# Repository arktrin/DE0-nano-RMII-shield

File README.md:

# DE0-nano_RMII
DE0-nano RMII shield

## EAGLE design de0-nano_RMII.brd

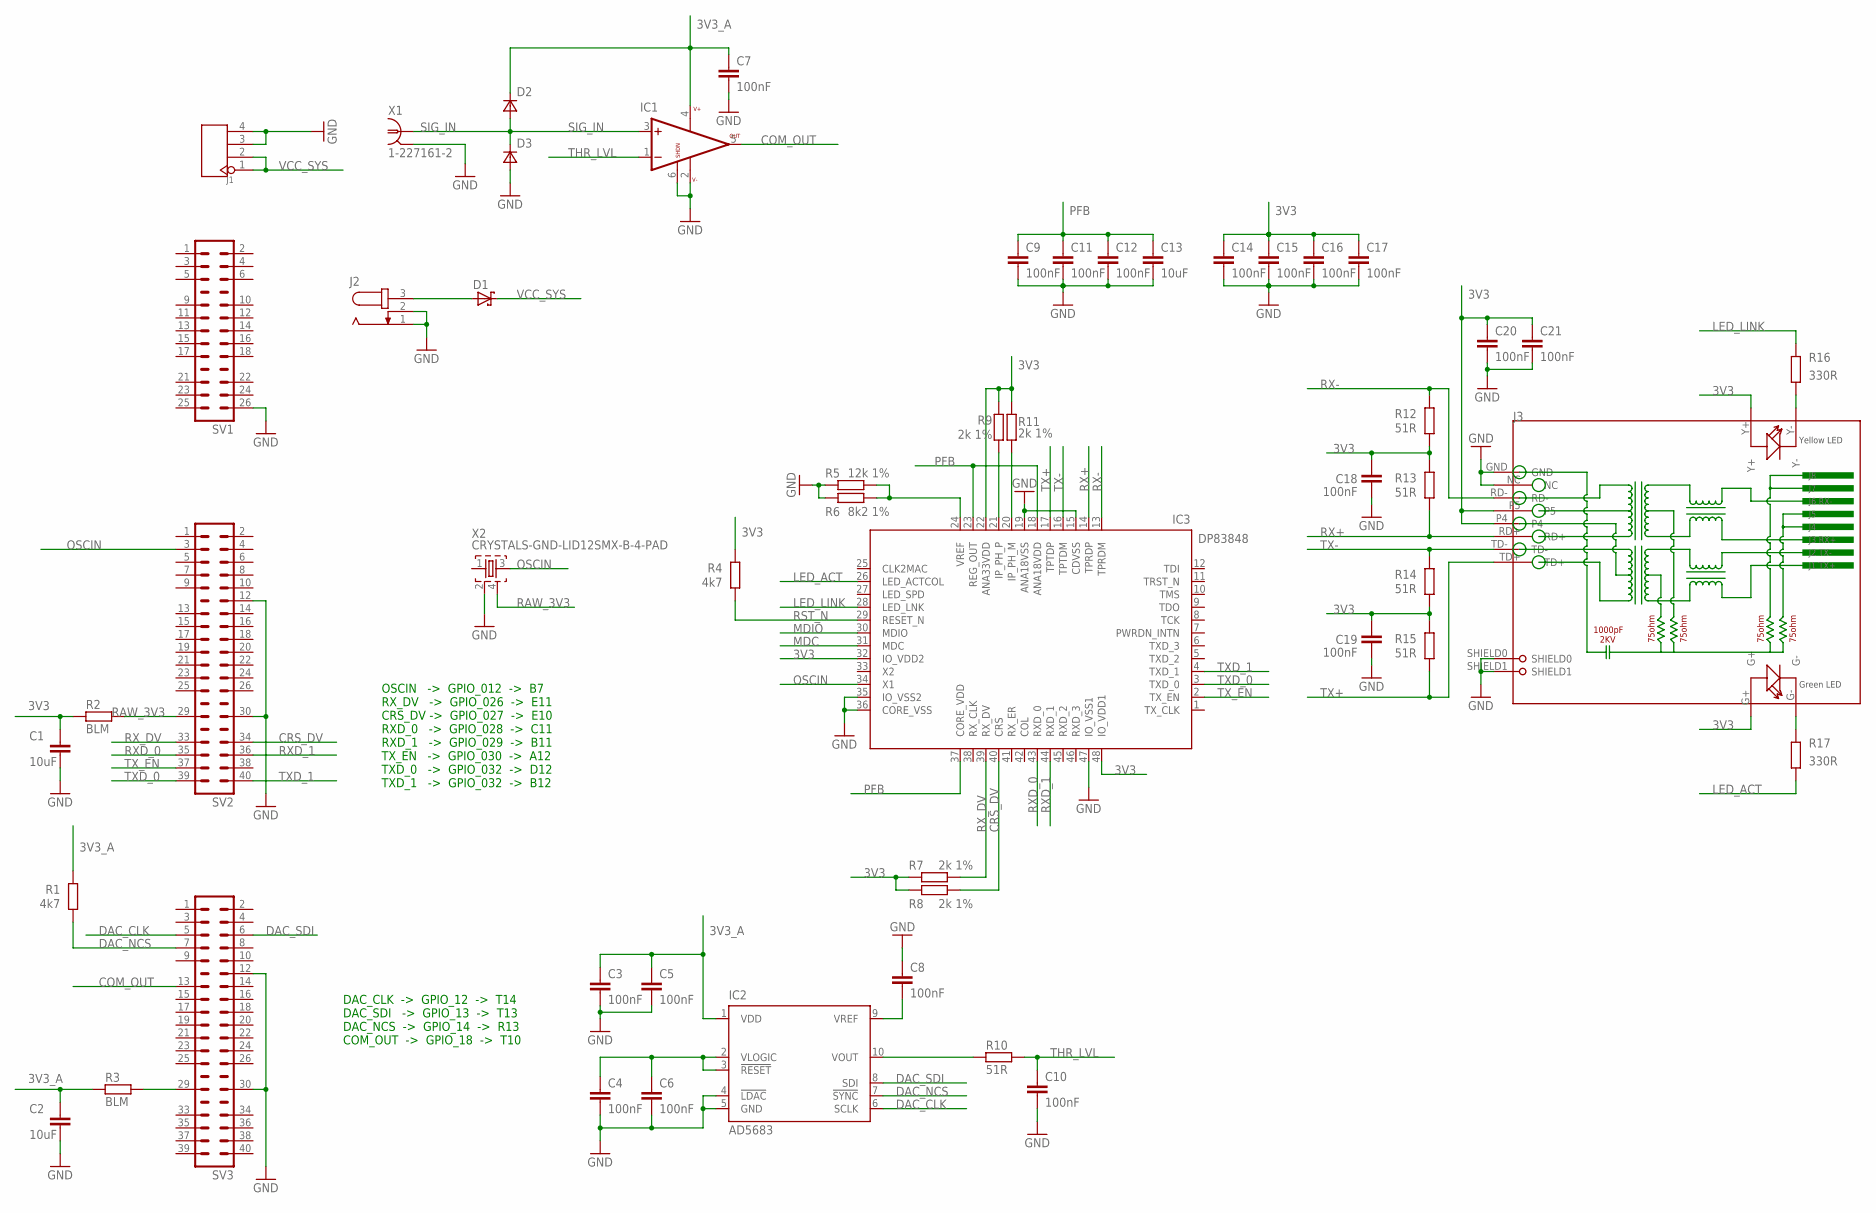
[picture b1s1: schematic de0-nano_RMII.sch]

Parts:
C1, C2, C13: 10uF; C0805
C3, C4, C5, C6, C7, C8, C9, C10, C11, C12, C14, C15, C16, C17, C18, C19, C20, C21: 100nF; C0603
D1: SCHOTTKY-DIODESMC; SMC
D2, D3: DSOD323; SOD323
IC1: LT1719; TSOT23-6
IC2: AD5683; SO10
IC3: DP83848; LQFP48
J1: HEADER-4P-60/35MIL; 4P-65/35MIL
J2: JACK-PLUG1; SPC4078
J3: RJ45-HR911105A-HR911105A; RJ45
R1, R4: 4k7; R0603
R2, R3: BLM; R0603
R5: 12k 1%; R0603
R6: 8k2 1%; R0603
R7, R8, R9, R11: 2k 1%; R0603
R10, R12, R13, R14, R15: 51R; R0603
R16, R17: 330R; R0603
SV1: MA13-2_ALT
SV2, SV3: MA20-2_ALT
X1: 1-227161-2; AMP_227161
X2: CRYSTALS-GND-LID12SMX-B-4-PAD; 7.5X5-4-PAD

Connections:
3V3: C1.1, C14.1, C15.1, C16.1, C17.1, C18.1, C19.1, C20.1, C21.1, IC3.22 (ANA33VDD), IC3.32 (IO_VDD2), IC3.48 (IO_VDD1), J3.G+, J3.P4, J3.P5, J3.Y+, R2.1, R4.1, R7.2, R8.2, R9.2, R11.2, R12.2, R13.1, R14.2, R15.1
3V3_A: C2.1, C3.1, C5.1, C7.1, D2.1 (C), IC1.4 (V+), IC2.1 (VDD), R1.1, R3.1
COM_OUT: IC1.5 (OUT), SV3.13
CRS_DV: IC3.40 (CRS), R8.1, SV2.34
DAC_CLK: IC2.6 (SCLK), SV3.5
DAC_NCS: IC2.7 (!SYNC), R1.2, SV3.7
DAC_SDI: IC2.8 (SDI), SV3.6
GND: C1.2, C2.2, C3.2, C4.2, C5.2, C6.2, C7.2, C8.2, C9.2, C10.2, C11.2, C12.2, C13.2, C14.2, C15.2, C16.2, C17.2, C18.2, C19.2, C20.2, C21.2, D3.2 (A), IC1.2 (V-), IC1.6 (SHDN), IC2.4 (!LDAC), IC2.5 (GND), IC3.15 (CDVSS), IC3.19 (ANA18VSS), IC3.35 (IO_VSS2), IC3.36 (CORE_VSS), IC3.47 (IO_VSS1), J1.3, J1.4, J2.1, J2.2, J3.GND, J3.NC, J3.SHIELD0, J3.SHIELD1, R5.2, R6.2, SV1.26, SV2.12, SV2.30, SV3.12, SV3.30, X1.2, X2.2
LED_ACT: IC3.26 (LED_ACTCOL), R17.1
LED_LINK: IC3.28 (LED_LNK), R16.2
MDC: IC3.31 (MDC)
MDIO: IC3.30 (MDIO)
unnamed: R3.2, SV3.29
unnamed: IC3.21 (IP_PH_P), R9.1
unnamed: J3.Y-, R16.1
unnamed: IC3.20 (IP_PH_M), R11.1
unnamed: J3.G-, R17.2
unnamed: IC2.10 (VOUT), R10.1
unnamed: IC3.24 (VREF), R5.1, R6.1
unnamed: C8.1, IC2.9 (VREF)
OSCIN: IC3.34 (X1), SV2.3, X2.3
PFB: C9.1, C11.1, C12.1, C13.1, IC3.18 (ANA18VDD), IC3.23 (REG_OUT), IC3.37 (CORE_VDD)
RAW_3V3: R2.2, SV2.29, X2.4
RST_N: IC3.29 (RESET_N), R4.2
RX+: IC3.14 (TPRDP), J3.RD+, R13.2
RX-: IC3.13 (TPRDM), J3.RD-, R12.1
RXD_0: IC3.43 (RXD_0), SV2.35
RXD_1: IC3.44 (RXD_1), SV2.36
RX_DV: IC3.39 (RX_DV), R7.1, SV2.33
SIG_IN: D2.2 (A), D3.1 (C), IC1.3 (+IN), X1.1
THR_LVL: C10.1, IC1.1 (-IN), R10.2
TX+: IC3.17 (TPTDP), J3.TD+, R15.2
TX-: IC3.16 (TPTDM), J3.TD-, R14.1
TXD_0: IC3.3 (TXD_0), SV2.39
TXD_1: IC3.4 (TXD_1), SV2.40
TX_EN: IC3.2 (TX_EN), SV2.37
VCC_SYS: D1.C, J1.1, J1.2
VLOGIC: C4.1, C6.1, IC2.2 (VLOGIC), IC2.3 (!RESET)
V_RAW: D1.A, J2.3

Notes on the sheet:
OSCIN -> GPIO_012 -> B7 RX_DV -> GPIO_026 -> E11 CRS_DV -> GPIO_027 -> E10 RXD_0 -> GPIO_028 -> C11 RXD_1 -> GPIO_029 -> B11 TX_EN -> GPIO_030 -> A12 TXD_0 -> GPIO_032 -> D12 TXD_1 -> GPIO_032 -> B12
DAC_CLK -> GPIO_12 -> T14 DAC_SDI -> GPIO_13 -> T13 DAC_NCS -> GPIO_14 -> R13 COM_OUT -> GPIO_18 -> T10

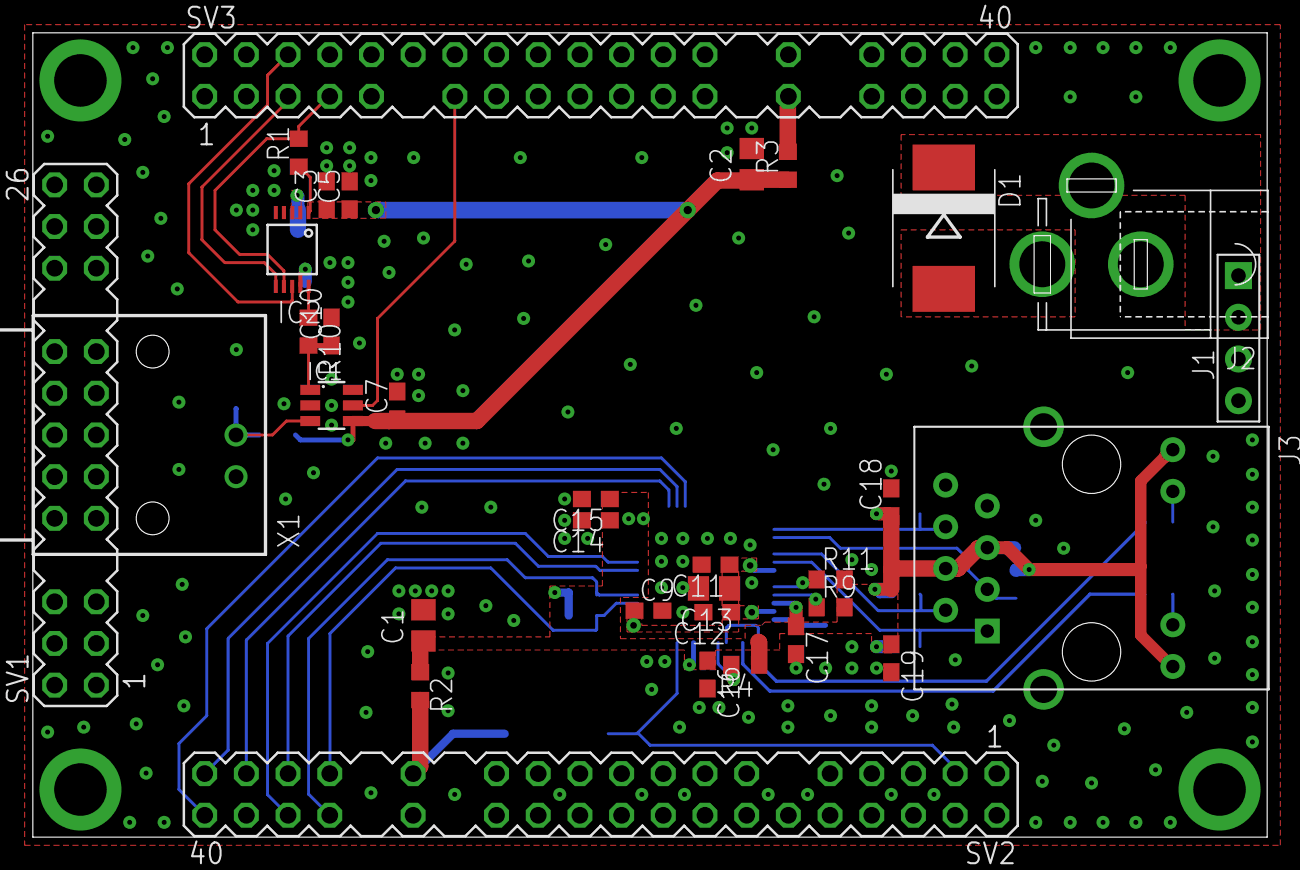
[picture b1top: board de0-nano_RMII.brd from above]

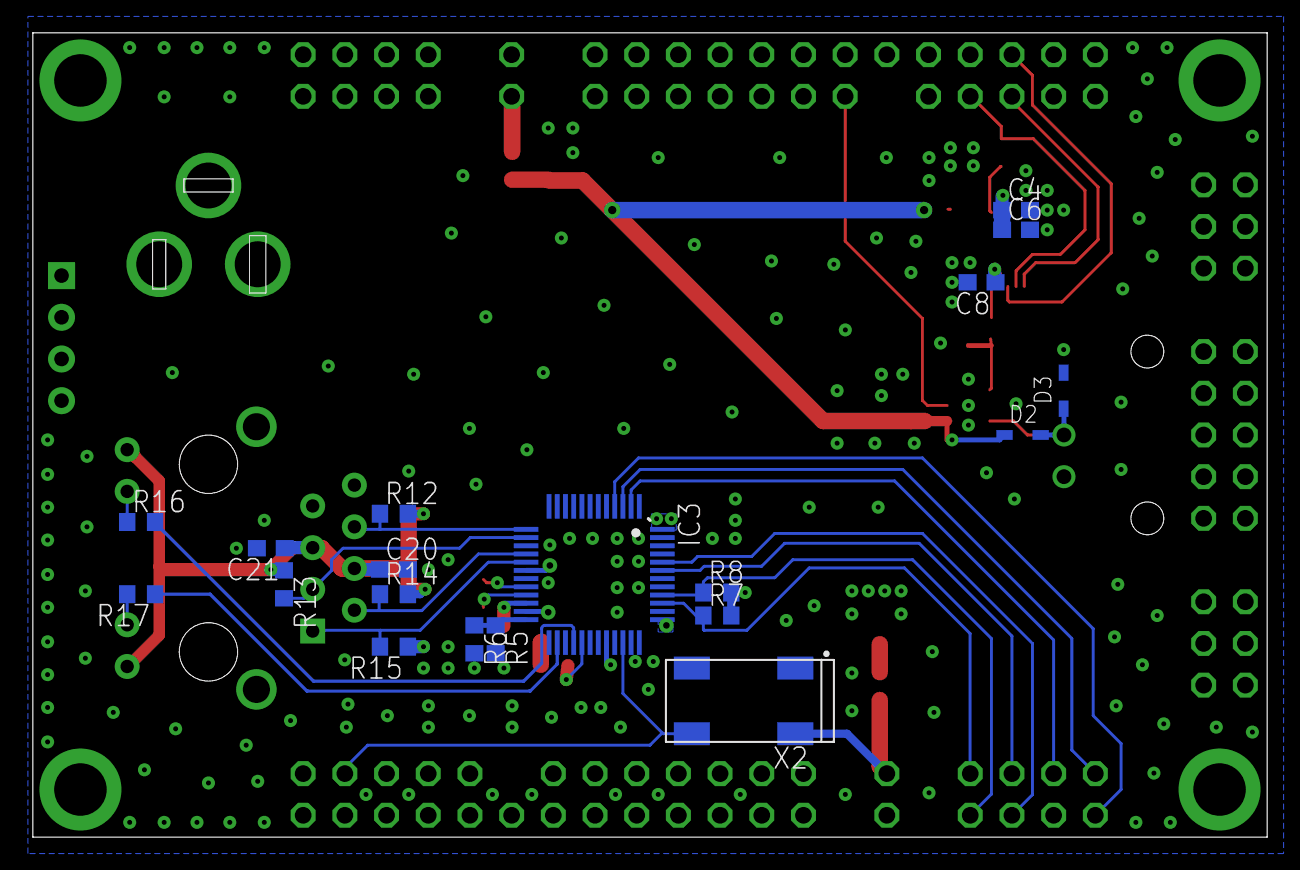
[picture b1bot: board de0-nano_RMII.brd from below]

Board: 2 copper layers, 75.2 x 49.0 mm, 52 parts (19 on the bottom side), 37 nets.

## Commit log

2017-02-26 real initial commit
2017-02-26 almost done
2017-02-27 RX_DV and CRS_DV added
2017-03-01 test branch
2017-03-01 removed some pads on connector
2017-03-02 added external power and DAC
2017-03-07 added protection diodes at the input, and separate crystal oscillator
2017-03-08 gerber generated
2023-09-02 add schematics in pdf
    its been a while [:
2023-09-02 abandon eagle, move to kicad
2023-09-02 fix kicad files location
2023-09-02 unhide LT1719 comparator name in schematics
